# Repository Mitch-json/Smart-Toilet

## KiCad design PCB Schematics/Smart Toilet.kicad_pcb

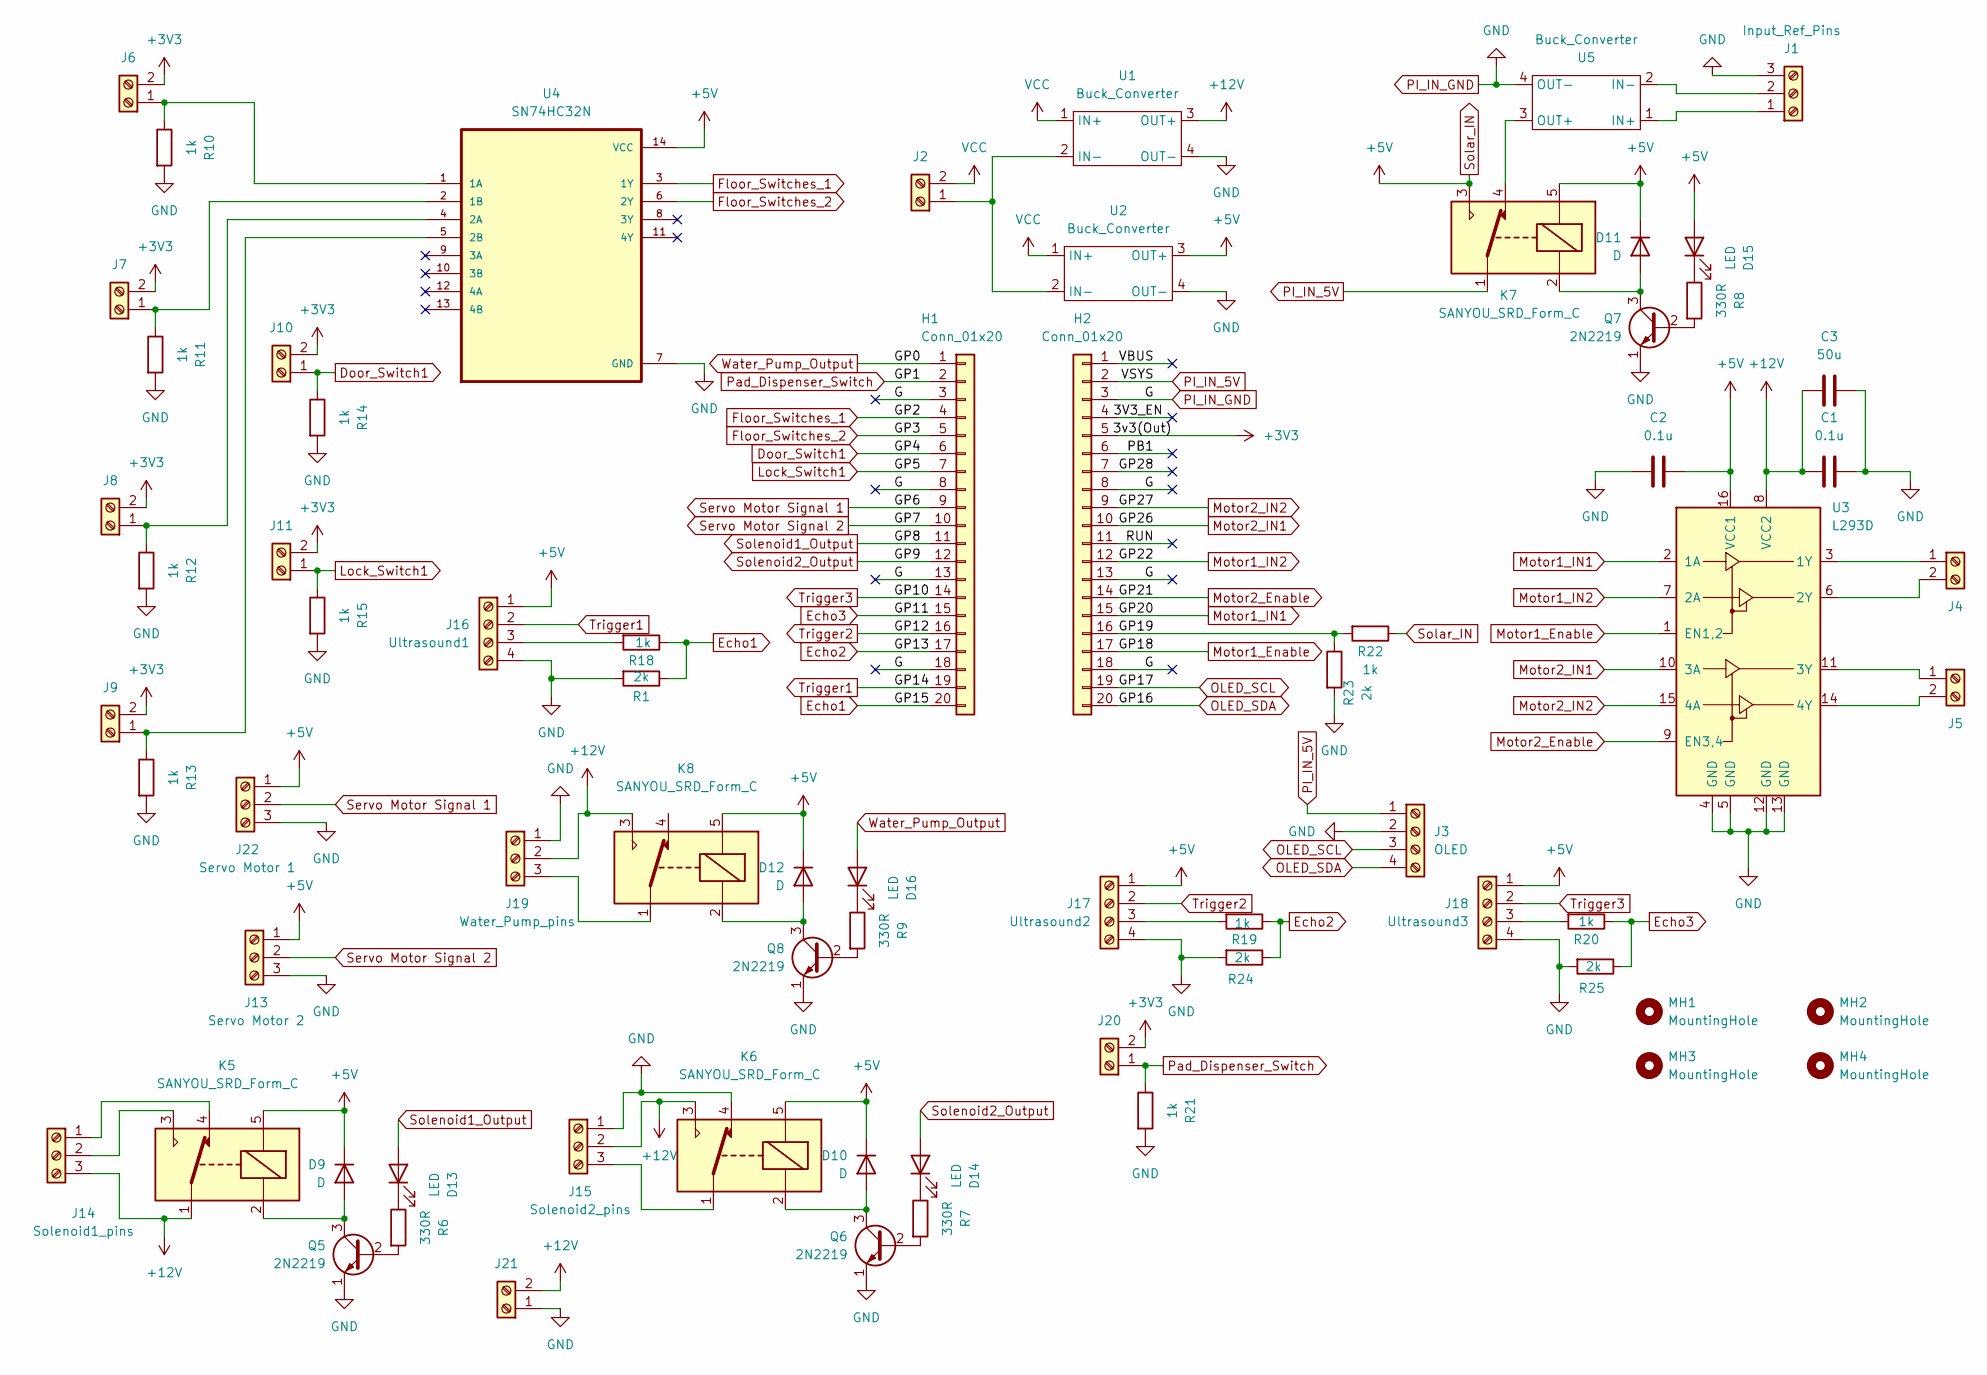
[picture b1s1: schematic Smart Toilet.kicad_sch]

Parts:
C1, C2: 0.1u; C_Disc_D4.7mm_W2.5mm_P5.00mm
C3: 50u; C_Radial_D6.3mm_H11.0mm_P2.50mm
D9, D10, D11, D12: D; D_A-405_P10.16mm_Horizontal
D13, D14, D15, D16: LED; LED_D5.0mm_IRBlack
H1, H2: Conn_01x20; PinSocket_1x20_P2.54mm_Vertical
J1: Input_Ref_Pins; TerminalBlock_MaiXu_MX126-5.0-03P_1x03_P5.00mm
J2, J6, J7, J8, J9, J10, J11, J20, J21: Screw_Terminal_01x02; TerminalBlock_MaiXu_MX126-5.0-02P_1x02_P5.00mm
J3: OLED; TerminalBlock_MaiXu_MX126-5.0-04P_1x04_P5.00mm
J4: Motor 1; TerminalBlock_MaiXu_MX126-5.0-02P_1x02_P5.00mm
J5: Motor 2; TerminalBlock_MaiXu_MX126-5.0-02P_1x02_P5.00mm
J13: Servo Motor 2; TerminalBlock_MaiXu_MX126-5.0-03P_1x03_P5.00mm
J14: Solenoid1_pins; TerminalBlock_MaiXu_MX126-5.0-03P_1x03_P5.00mm
J15: Solenoid2_pins; TerminalBlock_MaiXu_MX126-5.0-03P_1x03_P5.00mm
J16: Ultrasound1; TerminalBlock_MaiXu_MX126-5.0-04P_1x04_P5.00mm
J17: Ultrasound2; TerminalBlock_MaiXu_MX126-5.0-04P_1x04_P5.00mm
J18: Ultrasound3; TerminalBlock_MaiXu_MX126-5.0-04P_1x04_P5.00mm
J19: Water_Pump_pins; TerminalBlock_MaiXu_MX126-5.0-03P_1x03_P5.00mm
J22: Servo Motor 1; TerminalBlock_MaiXu_MX126-5.0-03P_1x03_P5.00mm
K5, K6, K7, K8: SANYOU_SRD_Form_C; Relay_SPDT_SANYOU_SRD_Series_Form_C
MH1, MH2, MH3, MH4: MountingHole; MountingHole_4.3mm_M4_DIN965_Pad
Q5, Q6, Q7, Q8: 2N2219; TO-92L_Inline_Wide
R1, R23, R24, R25: 2k; R_Axial_DIN0207_L6.3mm_D2.5mm_P10.16mm_Horizontal
R6, R7, R8, R9: 330R; R_Axial_DIN0207_L6.3mm_D2.5mm_P10.16mm_Horizontal
R10, R11, R12, R13, R14, R15, R18, R19, R20, R21, R22: 1k; R_Axial_DIN0207_L6.3mm_D2.5mm_P10.16mm_Horizontal
U1, U2, U5: Buck_Converter; Buck_converter
U3: L293D; DIP-16_W7.62mm
U4: SN74HC32N

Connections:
+3V3: H2.5, J6.2, J7.2, J8.2, J9.2, J10.2, J11.2, J20.2
+12V: C1.2, C3.2, J14.3, J15.2, J19.2, J21.2, K5.1, K6.3, K8.3, U1.3 (OUT+), U3.8 (VCC2)
/3V3_EN: H2.4
/GP19: H2.16, R22.2, R23.1
/GP28: H2.7
/PB1: H2.6
/RUN: H2.11
/VBUS: H2.1
Door_Switch1: H1.6, J10.1, R14.1
Echo1: H1.20, R1.1, R18.1
Echo2: H1.17, R19.1, R24.1
Echo3: H1.15, R20.1, R25.1
Floor_Switches_1: H1.4, U4.3 (1Y)
Floor_Switches_2: H1.5, U4.6 (2Y)
Lock_Switch1: H1.7, J11.1, R15.1
Motor1_Enable: H2.17, U3.1 (EN1,2)
Motor1_IN1: H2.15, U3.2 (1A)
Motor1_IN2: H2.12, U3.7 (2A)
Motor2_Enable: H2.14, U3.9 (EN3,4)
Motor2_IN1: H2.10, U3.10 (3A)
Motor2_IN2: H2.9, U3.15 (4A)
unnamed: D9.2 (A), K5.2, Q5.3 (C)
unnamed: D10.2 (A), K6.2, Q6.3 (C)
unnamed: D11.2 (A), K7.2, Q7.3 (C)
unnamed: D12.2 (A), K8.2, Q8.3 (C)
unnamed: D13.1 (K), R6.1
unnamed: D14.1 (K), R7.1
unnamed: D15.1 (K), R8.1
unnamed: D16.1 (K), R9.1
unnamed: J1.1, U5.1 (IN+)
unnamed: J1.2, U5.2 (IN-)
unnamed: J2.1, U1.2 (IN-), U2.2 (IN-)
unnamed: J4.1, U3.3 (1Y)
unnamed: J4.2, U3.6 (2Y)
unnamed: J5.1, U3.11 (3Y)
unnamed: J5.2, U3.14 (4Y)
unnamed: J6.1, R10.1, U4.1 (1A)
unnamed: J7.1, R11.1, U4.2 (1B)
unnamed: J8.1, R12.1, U4.4 (2A)
unnamed: J9.1, R13.1, U4.5 (2B)
unnamed: J14.1, K5.4
unnamed: J14.2, K5.3
unnamed: J15.3, K6.1
unnamed: J16.3, R18.2
unnamed: J17.3, R19.2
unnamed: J18.3, R20.2
unnamed: J19.3, K8.1
unnamed: Q5.2 (B), R6.2
unnamed: Q6.2 (B), R7.2
unnamed: Q7.2 (B), R8.2
unnamed: Q8.2 (B), R9.2
unnamed: K7.4, U5.3 (OUT+)
OLED_SCL: H2.19, J3.3
OLED_SDA: H2.20, J3.4
PI_IN_5V: H2.2, J3.1, K7.1
PI_IN_GND: C1.1, C2.2, C3.1, H1.3, H1.8, H1.13, H1.18, H2.3, H2.8, H2.13, H2.18, J1.3, J3.2, J13.3, J15.1, J16.4, J17.4, J18.4, J19.1, J21.1, J22.3, K6.4, Q5.1 (E), Q6.1 (E), Q7.1 (E), Q8.1 (E), R1.2, R10.2, R11.2, R12.2, R13.2, R14.2, R15.2, R21.2, R23.2, R24.2, R25.2, U1.4 (OUT-), U2.4 (OUT-), U3.4 (GND), U3.5 (GND), U3.12 (GND), U3.13 (GND), U4.7 (GND), U5.4 (OUT-)
Pad_Dispenser_Switch: H1.2, J20.1, R21.1
Servo Motor Signal 1: H1.9, J22.2
Servo Motor Signal 2: H1.10, J13.2
Solar_IN: C2.1, D9.1 (K), D10.1 (K), D11.1 (K), D12.1 (K), D15.2 (A), J13.1, J16.1, J17.1, J18.1, J22.1, K5.5, K6.5, K7.3, K7.5, K8.5, R22.1, U2.3 (OUT+), U3.16 (VCC1), U4.14 (VCC)
Solenoid1_Output: D13.2 (A), H1.11
Solenoid2_Output: D14.2 (A), H1.12
Trigger1: H1.19, J16.2
Trigger2: H1.16, J17.2
Trigger3: H1.14, J18.2
VCC: J2.2, U1.1 (IN+), U2.1 (IN+)
Water_Pump_Output: D16.2 (A), H1.1

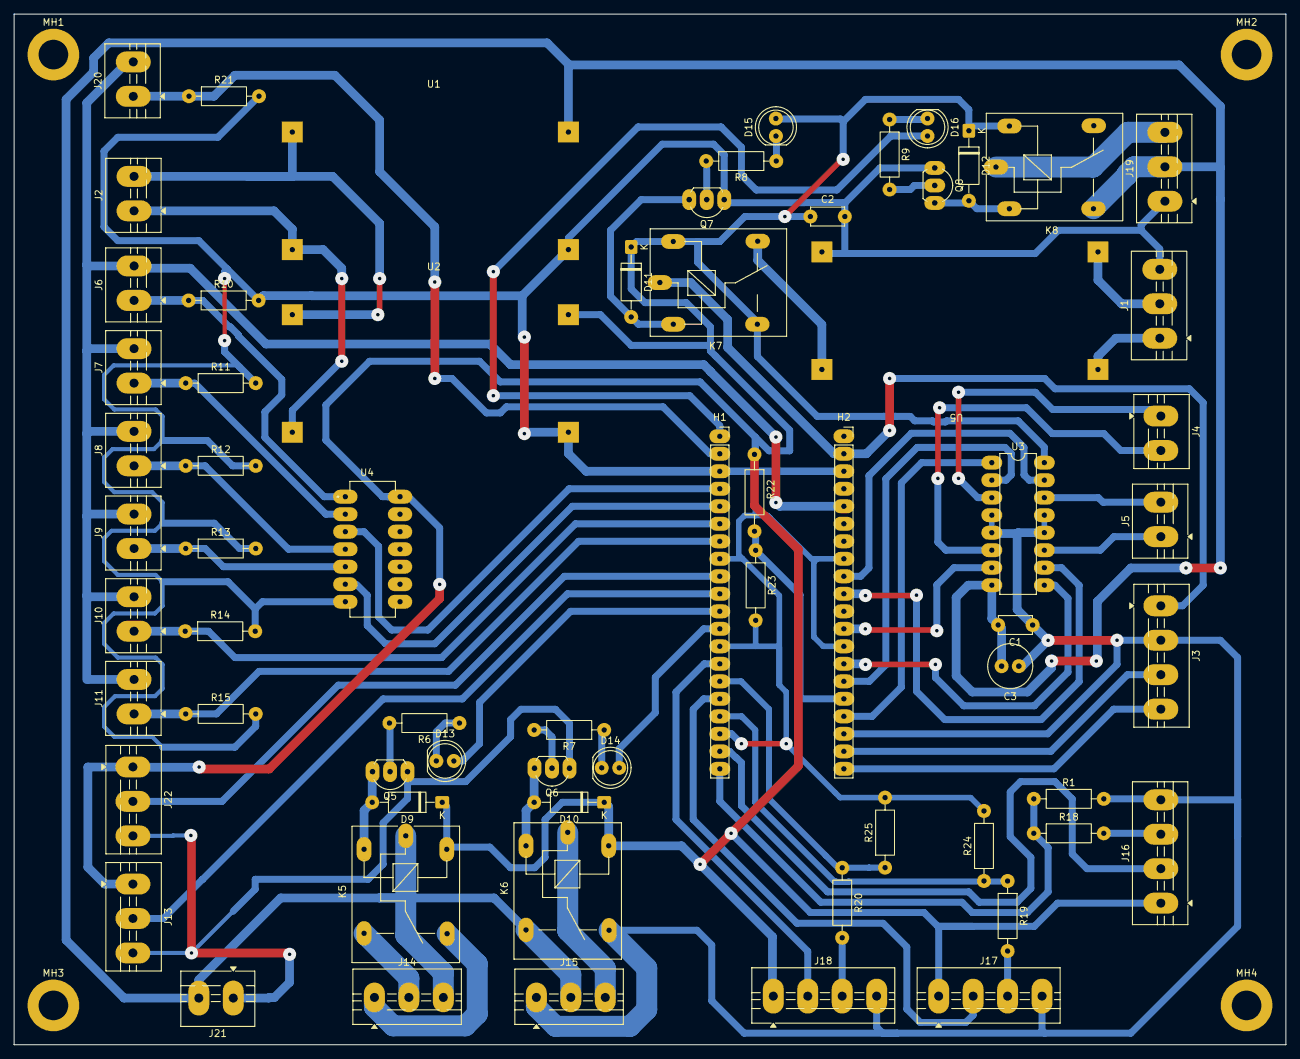
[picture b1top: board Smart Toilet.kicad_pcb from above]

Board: 2 copper layers, 184.5 x 149.5 mm, 70 parts (0 on the bottom side), 62 nets.

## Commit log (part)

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2026-06-28 Add Bulb Relay Logic
2026-06-29 Add Correct Bulb Relay Logic
